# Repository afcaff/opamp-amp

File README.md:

# Op-Amp Preamp

Single-channel audio preamp with gain, bass and treble controls, built around a TL072. I simulated it in PSpice, built it on a breadboard, then laid out a PCB in KiCad and measured both.

A phone or laptop plugs into the input and the output goes to a powered speaker. The gain knob turns the signal up to about 10x, and the bass and treble knobs boost or cut by about 12 dB.

## Demo video

https://github.com/user-attachments/assets/7785a830-bcad-4880-86f1-33a1208d45af

https://github.com/user-attachments/assets/1d51f3fe-2df7-4398-9d68-10ba9ee7a141

Labeled Circuit: 

## Specs

|                                                 | Target     | Calculated       | Breadboard (meter) | PCB (meter)      | PCB (scope)              |
| ----------------------------------------------- | ---------- | ---------------- | ------------------ | ---------------- | ------------------------ |
| Gain                                            | 0 to 20 dB | 0 to 20.8 dB*    | 0 to 21.4 dB       | 0 to 19.7 dB     | 0 to 19.6 dB             |
| Flat response (both tone pots centered, 400 Hz) | ±1 dB      | 0 dB             | +0.6 dB            | −0.3 dB          | 0 dB                     |
| Bass at 50 Hz                                   | ±12 dB     | +8.2 / −8.2 dB   | +8.3 / −8.5 dB     | +8.1 / −8.3 dB   | +8.3 / −8.1 dB           |
| Treble at 10 kHz                                | ±12 dB     | +11.2 / −11.2 dB | +11.8 / −12.5 dB   | +12.2 / −12.4 dB | +11.4 / cut failed (pot) |
| Virtual ground                                  | 7.5 V      | 7.5 V            | 7.48 V             | 7.38 V        | —                        |

## Circuit

The first half of the TL072 is a non-inverting amp. R<sub>G</sub> is 10k and R<sub>F</sub> is a 100k pot, so the gain goes from 1 (0 dB) to 11 (20.8 dB). C<sub>G</sub> (47µF) in series with R<sub>G</sub> keeps the DC gain at 1 so the output offset stays small.

The second half is a Baxandall tone control. A lot of published versions use 10k resistors around the pots, which gives around ±20 dB. I used 33k so the gain at the ends of the pot is (100k + 33k) / 33k ≈ 4, which is 12 dB.

- Bass: R<sub>B</sub> = 33k, C<sub>B</sub> = 33nF (turnover target 50 Hz), 100k linear pot
- Treble: R<sub>T</sub> = 11k, C<sub>T</sub> = 4.7nF (turnover target 3 kHz), 100k linear pot

It runs on a single 15 V supply. The TLE2426 makes a 7.5 V virtual ground so the op amps can swing both ways around it.

Hand calculations: [measure/HandCalcs.pdf](measure/HandCalcs.pdf)

Full circuit simulation: [FullCircuitsim/](FullCircuitsim/)

## PCB
After verifying everything on the breadboard, I designed a two layer board in KiCad. Every part is through-hole and designed for hand soldering. The pots and audio jacks mount directly to the board.

Finished PCB:

Schematic: [docs/PrintUSchematic.pdf](docs/PrintUSchematic.pdf)

### Board
| Item | Value |
|---|---|
| Size | about 100 × 60 mm |
| Layers | 2 (signals on top, VGround on bottom) |
| Parts | through-hole, TL072 and TLE2426 in DIP-8 sockets |
| Power input | 2 pin screw terminal, 15 V, with a series diode  |
| Decoupling | 100 µF + 100 nF at the supply input, 100 nF next to the TL072 |
| Traces | 0.4 mm signal, 0.8 mm power |
| Mounting | M3 holes for standoffs |
## PCB measurements

### Gain stage (400 Hz)

| Gain pot | In (V) | Out (V) | Gain  | dB   | Scope (dB) | Calculated (dB) |
| -------- | ------ | ------- | ----- | ---- | ---------- | --------------- |
| Min      | 0.097  | 0.096   | 0.99x | −0.1 | −0.1       | 0               |
| Half     | 0.097  | 0.541   | 5.6x  | 14.9 | 14.7       | 14.5            |
| Max      | 0.097  | 0.941   | 9.7x  | 19.7 | 19.6       | 19.7            |
 
### Tone stage
 
Bass at 50 Hz:
 
| Bass pot   | In (V) | Out (V) | Gain  | dB   | Scope (dB) |
| ---------- | ------ | ------- | ----- | ---- | ---------- |
| Full cut   | 0.119  | 0.046   | 0.39x | −8.3 | −8.1       |
| Center     | 0.119  | 0.120   | 1.01x | +0.1 | +0.1       |
| Full boost | 0.119  | 0.304   | 2.55x | +8.1 | +8.3       |
 
Treble at 10 kHz:
 
| Treble pot | In (V) | Out (V) | Gain  | dB    | Scope (dB)        |
| ---------- | ------ | ------- | ----- | ----- | ----------------- |
| Full cut   | 0.096  | 0.023   | 0.24x | −12.4 | failed (worn pot) |
| Center     | 0.096  | 0.094   | 0.98x | −0.2  | +0.2              |
| Full boost | 0.096  | 0.393   | 4.09x | +12.2 | +11.4             |

### Files
- Oscilloscope captures: [`measure/scope`](measure/scope)
- KiCad project: [`kicad/`](kicad/) 
- Gerbers: [`kicad/audiopamp/gerber.zip`](kicad/audiopamp/gerber.zip)

## Breadboard measurements

All readings were taken with a multimeter on AC volts, black probe on the virtual ground, using sine tones from a laptop.

### Gain stage (400 Hz)

Gain stage demo: 

https://github.com/user-attachments/assets/f91d0bfd-d7b4-4a68-a31d-0bf0310b4c41

| Gain pot | In (V) | Out (V) | Gain | dB | PSpice (dB) |
|---|---|---|---|---|---|
| Min | 0.014 | 0.014 | 1.0x | 0 | 0 |
| Half | 0.014 | 0.095 | 6.8x | 16.6 | 15.6 |
| Max | 0.014 | 0.165 | 11.8x | 21.4 | 20.8 |

The input was only 14 mV, which limits the meter to about ±7%, so these are within the meter's accuracy.

### Tone stage

Gain is the tone stage output (pin 7) divided by its input.

Bass at 50 Hz:

| Bass pot | In (V) | Out (V) | Gain | dB |
|---|---|---|---|---|
| Full cut | 0.254 | 0.096 | 0.38x | −8.5 |
| Center | 0.254 | 0.245 | 0.96x | −0.3 |
| Full boost | 0.254 | 0.657 | 2.59x | +8.3 |

Treble at 10 kHz:

| Treble pot | In (V) | Out (V) | Gain | dB |
|---|---|---|---|---|
| Full cut | 0.126 | 0.030 | 0.24x | −12.5 |
| Center | 0.126 | 0.127 | 1.01x | +0.1 |
| Full boost | 0.126 | 0.491 | 3.90x | +11.8 |

At 1 kHz the bass knob does nothing (within 0.1 dB) and the treble knob moves the level by about ±1.8 dB, since the treble shelf starts around 3 kHz.

## Problems I ran into
 
### Breadboard
 
- **60 Hz hum.** Ground loop between the bench supply and the speaker on its wall charger. Gone with the speaker on battery.
- **Channels seemed to swap.** The STX-3000 jack tabs made bad contact in the breadboard. Soldering Dupont leads to the tabs fixed it.
- **"No signal."** Laptop volume was at 10%, so the gain stage output was only 7 mV. At 100% the 50 Hz tone distorted and shrank the bass range, so I measured at about 70%.

### PCB
 
- **Dead TL072.** Both outputs were stuck near the positive rail, the board drew 20 to 36 mA, and the TLE2426 got warm. A new chip fixed it. Now I check DC at every op amp pin before putting audio in.
- **Worn treble pot.** At full cut the 10 kHz output came out about 1.2x the input instead of 0.24x, and there was static below about 40% cut. The joints and traces checked out, so the wiper is losing contact on the worn cut side of the track. I need to replace the 100k Pot.

## Equations

Non-inverting gain:

$$\frac{V_o}{V_i} = 1 + \frac{R_F}{R_G}$$

Gain in dB:

$$A_V[\text{dB}] = 20\log\left(\frac{V_o}{V_i}\right)$$

Filter frequency:

$$f = \frac{1}{2\pi RC}$$

## Software

PSpice, KiCad

## Resources

Rod Elliott's site [sound-au.com](https://sound-au.com/index.html) explained most of what I needed for this project.

[Learn About Electronics: Baxandall tone control](https://learnabout-electronics.org/Amplifiers/amplifiers42.php) explains how the bass and treble controls work and what the response looks like.

[This video](https://www.youtube.com/watch?v=f8DllUXnWA0) helped me see which path each frequency takes through the tone circuit.

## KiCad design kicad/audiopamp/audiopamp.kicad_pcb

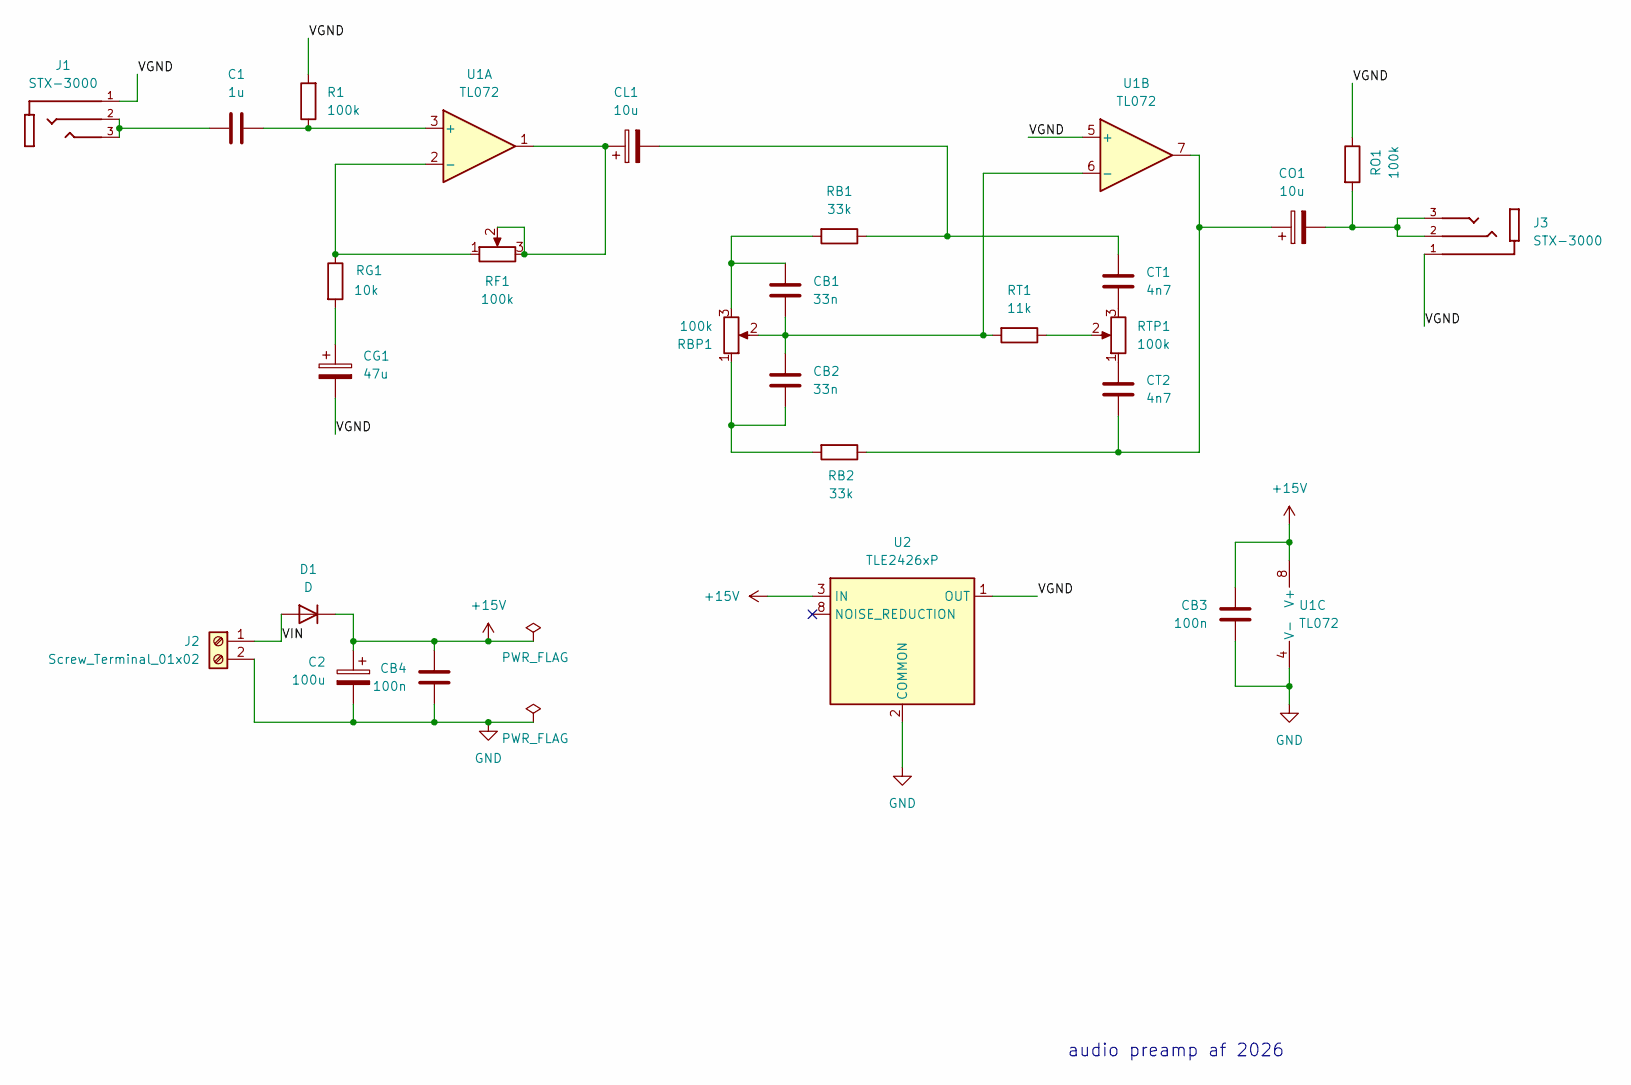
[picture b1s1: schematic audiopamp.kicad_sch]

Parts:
C1: 1u; C_Rect_L7.2mm_W5.5mm_P5.00mm_FKS2_FKP2_MKS2_MKP2
C2: 100u; CP_Radial_D5.0mm_P2.00mm
CB1, CB2: 33n; C_Rect_L7.2mm_W5.5mm_P5.00mm_FKS2_FKP2_MKS2_MKP2
CB3, CB4: 100n; C_Rect_L7.2mm_W5.5mm_P5.00mm_FKS2_FKP2_MKS2_MKP2
CG1: 47u; CP_Radial_D5.0mm_P2.00mm
CL1: 10u; CP_Radial_D5.0mm_P2.00mm
CO1: 10u; CP_Radial_D5.0mm_P2.00mm
CT1, CT2: 4n7; C_Rect_L7.2mm_W5.5mm_P5.00mm_FKS2_FKP2_MKS2_MKP2
D1: D; D_DO-41_SOD81_P10.16mm_Horizontal
J1, J3: STX-3000; KYCON_STX-3000
J2: Screw_Terminal_01x02; TerminalBlock_Phoenix_MKDS-1,5-2-5.08_1x02_P5.08mm_Horizont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
R1: 100k; R_Axial_DIN0207_L6.3mm_D2.5mm_P10.16mm_Horizontal
RB1, RB2: 33k; R_Axial_DIN0207_L6.3mm_D2.5mm_P10.16mm_Horizontal
RBP1: 100k; pdb12-M
RF1: 100k; pdb12-M
RG1: 10k; R_Axial_DIN0207_L6.3mm_D2.5mm_P10.16mm_Horizontal
RO1: 100k; R_Axial_DIN0207_L6.3mm_D2.5mm_P10.16mm_Horizontal
RT1: 11k; R_Axial_DIN0207_L6.3mm_D2.5mm_P10.16mm_Horizontal
RTP1: 100k; pdb12-M
U1: TL072; DIP-8_W7.62mm_Socket
U2: TLE2426xP; DIP-8_W7.62mm_Socket

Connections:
+15V: C2.1, CB3.2, CB4.2, D1.1 (K), U1.8 (V+), U2.3 (IN)
/VGND: CG1.2, J1.1, J3.1, R1.2, RO1.1, U1.5 (+), U2.1 (OUT)
/VIN: D1.2 (A), J2.1
GND: C2.2, CB3.1, CB4.1, J2.2, U1.4 (V-), U2.2 (COMMON)
unnamed: C1.1, J1.2, J1.3
unnamed: CB1.2, RB1.2, RBP1.3
unnamed: CB2.1, RB2.2, RBP1.1
unnamed: CG1.1, RG1.2
unnamed: CL1.1, RF1.2, RF1.3, U1.1
unnamed: CL1.2, CT1.2, RB1.1
unnamed: CO1.1, CT2.2, RB2.1, U1.7
unnamed: CO1.2, J3.2, J3.3, RO1.2
unnamed: CT1.1, RTP1.3
unnamed: CT2.1, RTP1.1
unnamed: RT1.1, RTP1.2
unnamed: C1.2, R1.1, U1.3 (+)
unnamed: RF1.1, RG1.1, U1.2 (-)
unnamed: CB1.1, CB2.2, RBP1.2, RT1.2, U1.6 (-)

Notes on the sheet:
audio preamp af 2026

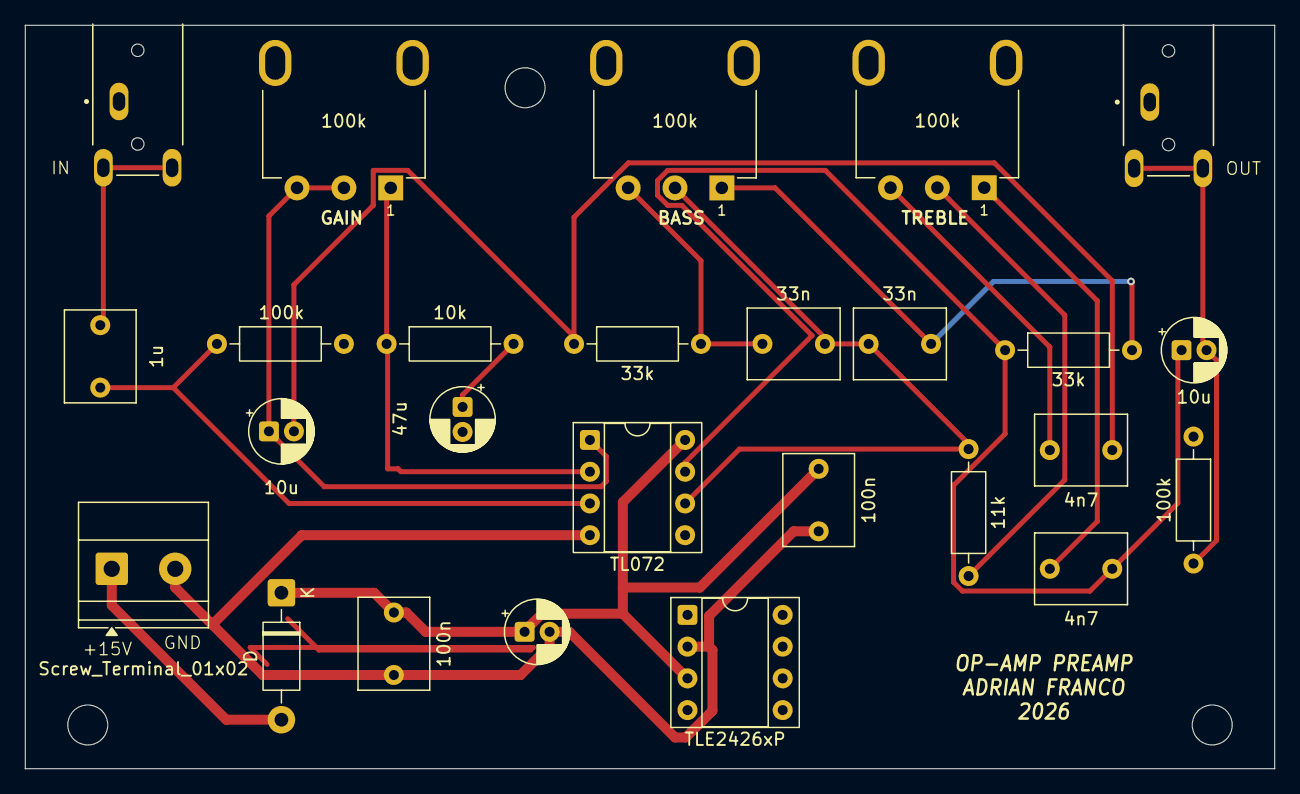
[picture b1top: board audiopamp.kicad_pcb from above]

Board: 2 copper layers, 100.0 x 59.5 mm, 26 parts (0 on the bottom side), 18 nets.
